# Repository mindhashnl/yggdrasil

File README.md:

# 🌳 Yggdrasil - Hardware Infrastructure

> **⚠️ NOTE:** This repository contains **hardware design files only** (Schematics, PCB Layouts, Gerber files, BOMs, and Mechanical CAD). 
> The software stack is not yet updated to the new hardware.

## 📖 Overview

Yggdrasil is an open-source, modular hardware-in-the-loop (HIL) testing framework designed for continuous integration (CI/CD) of embedded systems. It allows developers to test firmware automatically on real microcontrollers (MCUs) at scale. 

The physical architecture is designed to fit inside a standard **19-inch 3U server rack** and consists of a primary control board, a multiplexing backplane, and hot-swappable target testing blades.

---

## 🧩 System Architecture

The hardware is split into three main modules:

### 1. Mimir (Compute Controller)
The "brain" of the server. It acts as the bridge between the high-level network and the low-level hardware matrix.
* **Core:** Raspberry Pi Compute Module 5 (CM5).
* **Storage:** M.2 NVMe SSD slot for reliable, high-speed storage.
* **Connectivity:** Gigabit Ethernet (RJ45), USB-A, HDMI (for local debugging).
* **Interface:** Connects to the backplane via a custom-pinned PCIe x8 mechanical connector.

### 2. Bifrost (The Backplane)
The routing matrix that connects Mimir to the testing blades. It contains no "smart" compute chips, only routing and switching logic.
* **Switching:** Uses cascaded `74HC595` and `SN74HCS165` shift registers to control `TMUX1511` analog multiplexers.
* **Buses:** Routes shared JTAG, UART, SPI, I2C, CAN, and GPIO lines to any connected blade.
* **Power:** Accepts 12V input and steps it down to 5V and 3.3V rails for the entire system using TPSM33625 modules.
* **Capacity:** Supports up to 16 daughter boards.

### 3. Valkyrie (Daughter Blades)
The Device-Under-Test (DUT) modules. These are inserted into the front of the server.
* **Form Factor:** 110mm x 170mm (excluding PCIe fingers). Fits in custom HDD-style hot-swap trays.
* **Standardization:** Connects to Bifrost using a custom-pinned PCIe x16 mechanical connector.
* **Included Reference Designs:**
  * **Valkyrie-ESP32S3:** A complete testing blade featuring an ESP32-S3, status LEDs, physical buttons, and a hardware identification EEPROM.
  * **Valkyrie-Test:** A diagnostic board with LEDs mapped to every PCIe lane to visually verify multiplexer switching logic.

---

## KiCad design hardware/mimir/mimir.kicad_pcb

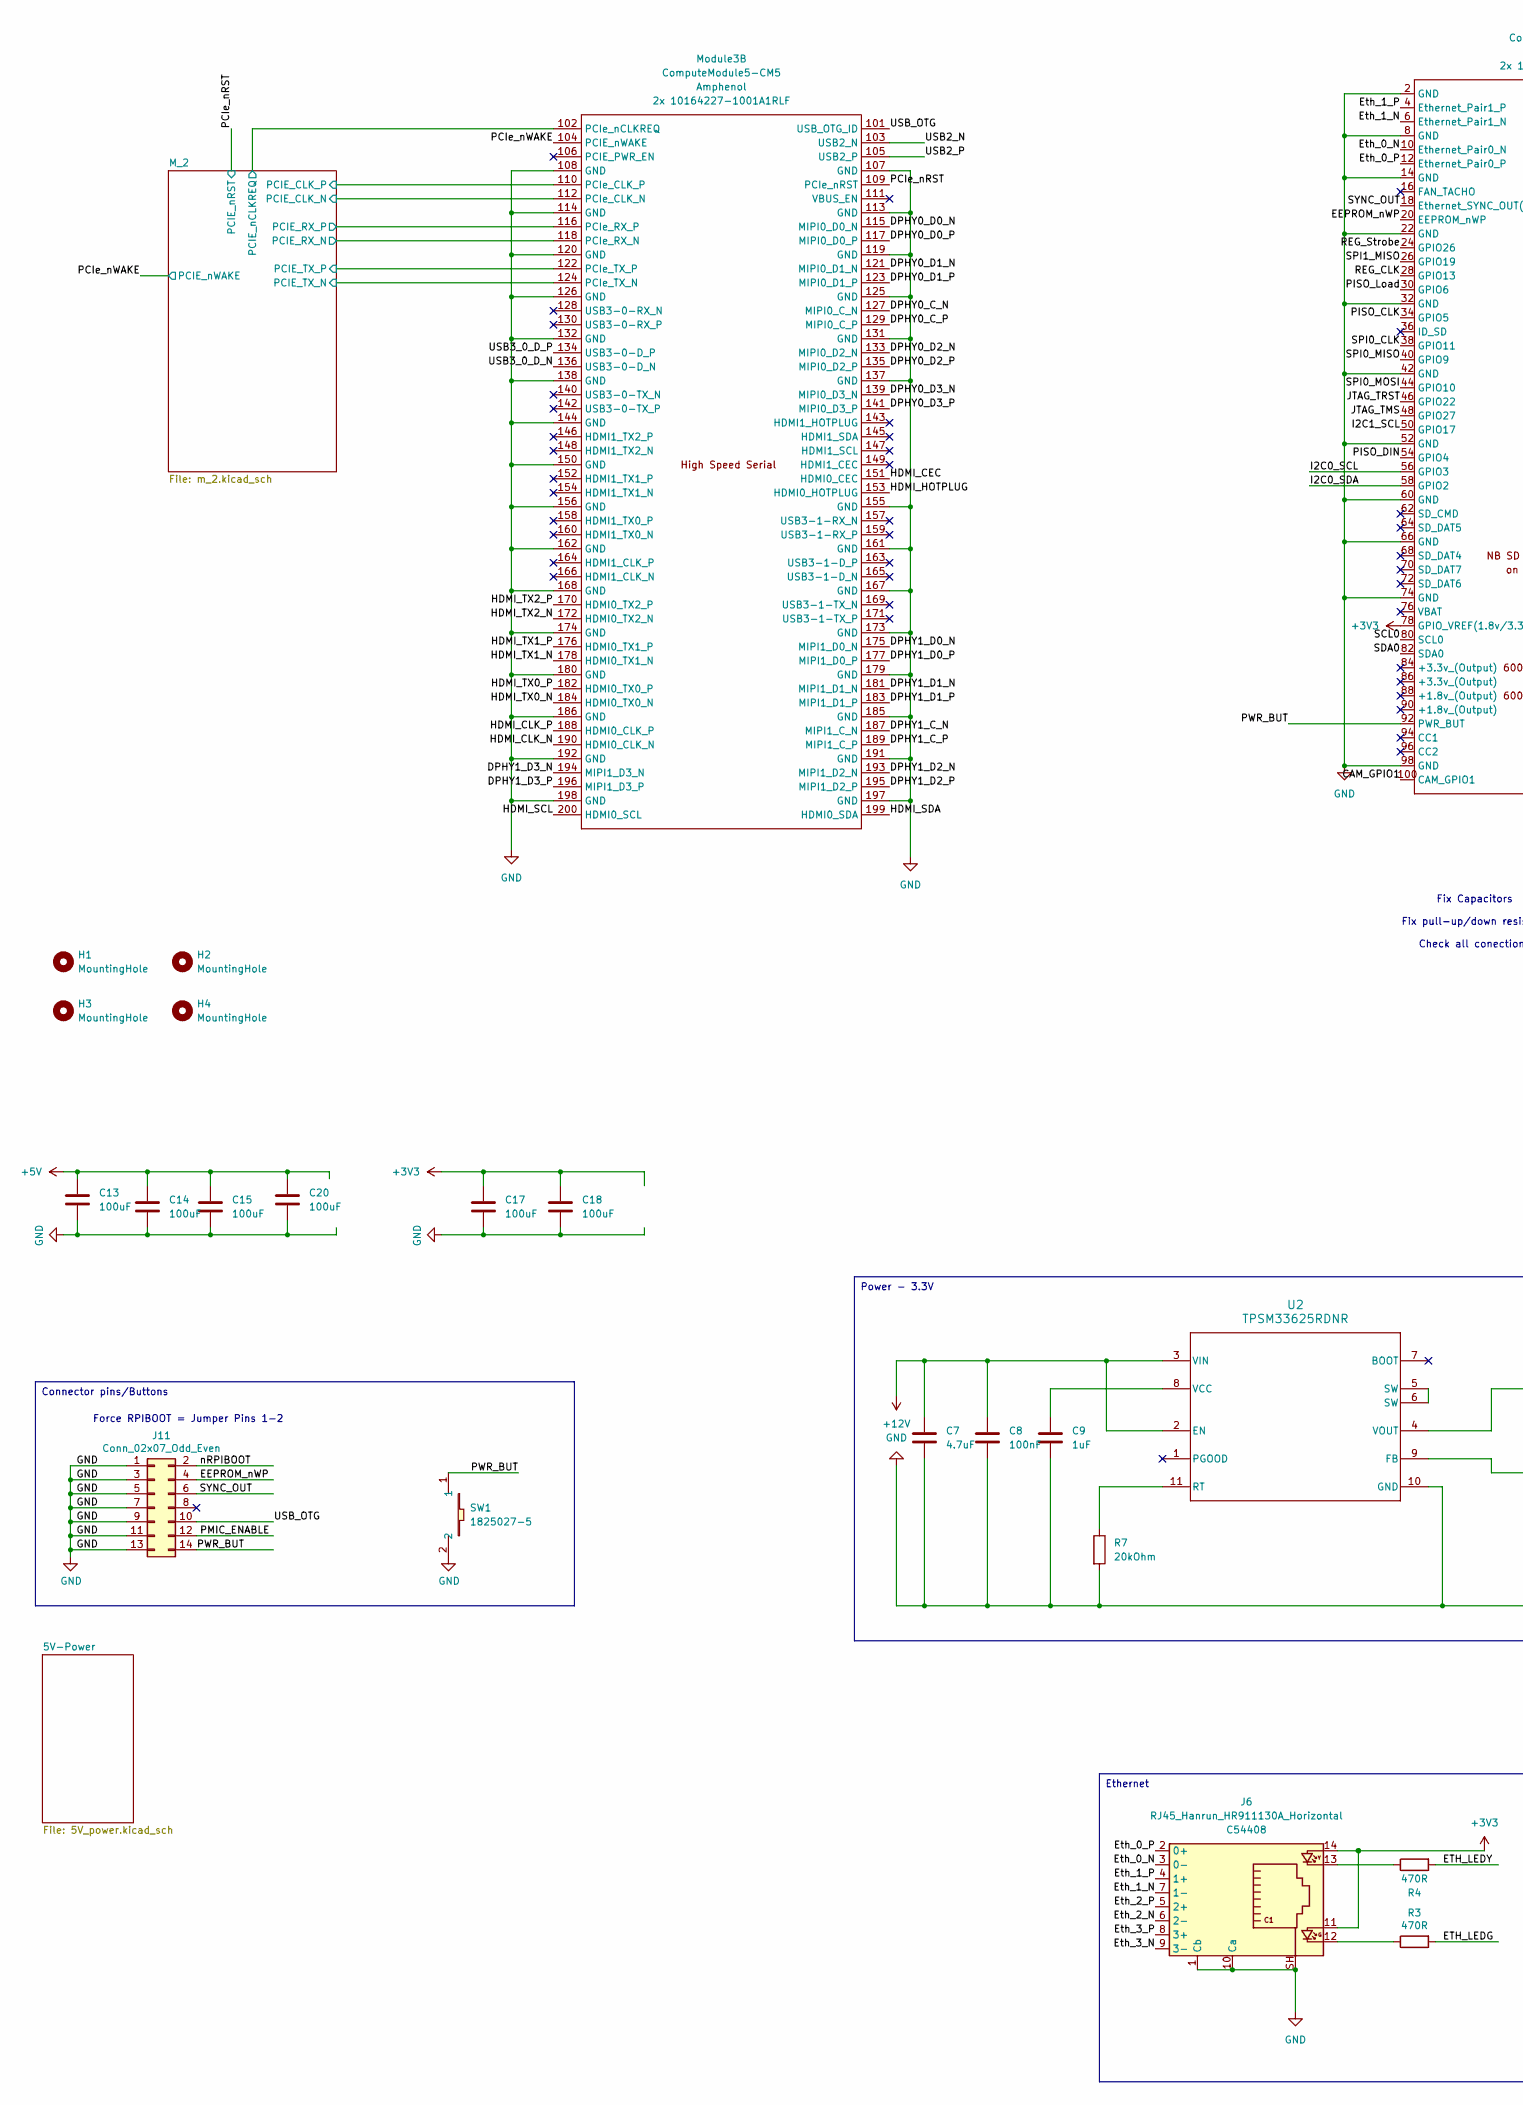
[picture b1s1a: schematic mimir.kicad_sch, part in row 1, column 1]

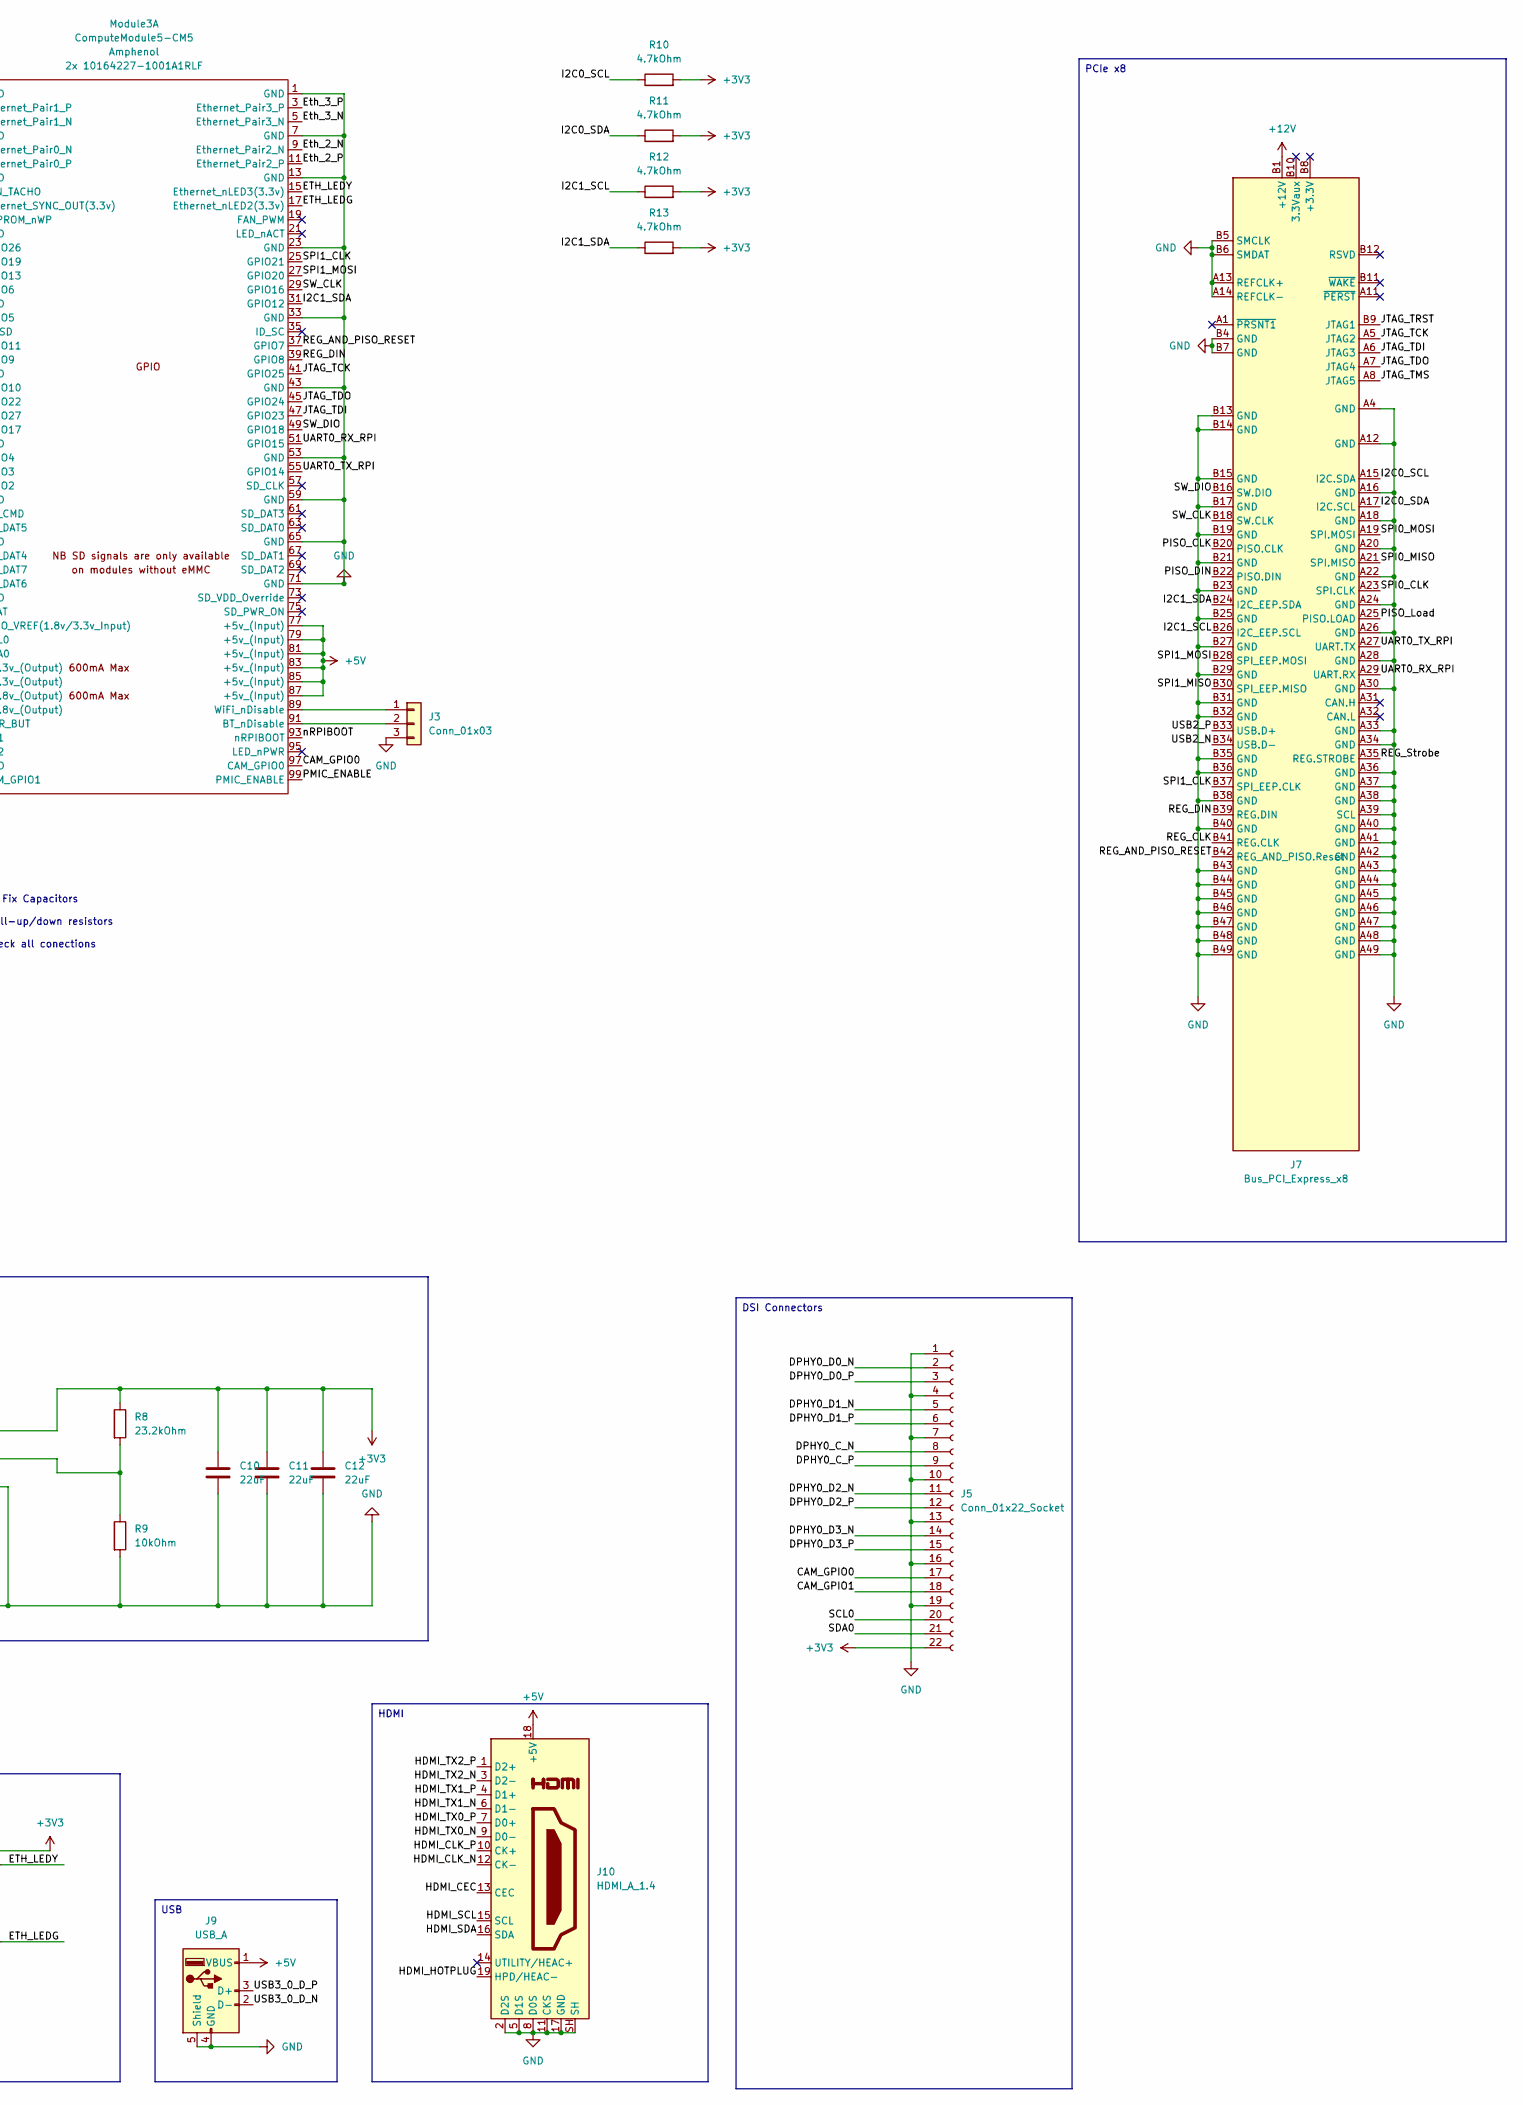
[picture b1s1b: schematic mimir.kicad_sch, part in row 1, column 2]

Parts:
C7: 4.7uF; C_0805_2012Metric
C8: 100nF; C_0805_2012Metric
C9: 1uF; C_0805_2012Metric
C10, C11, C12: 22uF; C_0805_2012Metric
C13, C14, C15, C17, C18, C20: 100uF; C_1210_3225Metric
H1, H2, H3, H4: MountingHole; MountingHole_3.2mm_M3_DIN965_Pad_TopBottom
J3: Conn_01x03; PinHeader_1x03_P2.54mm_Vertical
J5: Conn_01x22_Socket; Hirose_FH12-22S-0.5SH_1x22-1MP_P0.50mm_Horizontal
J6: RJ45_Hanrun_HR911130A_Horizontal; MPN C54408
J7: Bus_PCI_Express_x8; BUS_PCIexpress_x8
J9: USB_A; USB_A_Molex_67643_Horizontal
J10: HDMI_A_1.4; HDMI_A_Molex_208658-1001_Horizontal
J11: Conn_02x07_Odd_Even; PinHeader_2x07_P2.54mm_Vertical; Part Description PinHeader_2x07_P2.54mm_Vertical
Module3: ComputeModule5-CM5; Raspberry-Pi-5-Compute-Module; MPN C597931
R3, R4: 470R; R_0805_2012Metric; Part Description Resistor 470R M1005 1% 63mW
R7: 20kOhm; R_0805_2012Metric
R8: 23.2kOhm; R_0805_2012Metric
R9: 10kOhm; R_0805_2012Metric
R10, R11, R12, R13: 4.7kOhm; R_0805_2012Metric
SW1: 1825027-5; KEY-TH_4P-L7.5-W6.8-P4.50-LS7.2; LCSC Part C86476
U2: TPSM33625RDNR; RDN0011A-MFG_custom

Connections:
+3V3: C10.1, C11.1, C12.1, C17.1, C18.1, J5.22, J6.11, J6.14, Module3.78 (GPIO_VREF(1.8v/3.3v_Input)), R8.1, R10.2, R11.2, R12.2, R13.2, U2.4 (VOUT); also elsewhere on the board
+5V: C13.1, C14.1, C15.1, C20.1, J9.1 (VBUS), J10.18 (+5V), Module3.77 (+5v_(Input)), Module3.79 (+5v_(Input)), Module3.81 (+5v_(Input)), Module3.83 (+5v_(Input)), Module3.85 (+5v_(Input)), Module3.87 (+5v_(Input)); also elsewhere on the board
+12V: C7.1, C8.1, J7.A2 (+12V), J7.A3 (+12V), J7.B1 (+12V), J7.B2 (+12V), J7.B3 (+12V), U2.2 (EN), U2.3 (VIN); also elsewhere on the board
/CAM_GPIO0: J5.17, Module3.97 (CAM_GPIO0)
/CAM_GPIO1: J5.18, Module3.100 (CAM_GPIO1)
/DPHY0_C_N: J5.8, Module3.127 (MIPI0_C_N)
/DPHY0_C_P: J5.9, Module3.129 (MIPI0_C_P)
/DPHY0_D0_N: J5.2, Module3.115 (MIPI0_D0_N)
/DPHY0_D0_P: J5.3, Module3.117 (MIPI0_D0_P)
/DPHY0_D1_N: J5.5, Module3.121 (MIPI0_D1_N)
/DPHY0_D1_P: J5.6, Module3.123 (MIPI0_D1_P)
/DPHY0_D2_N: J5.11, Module3.133 (MIPI0_D2_N)
/DPHY0_D2_P: J5.12, Module3.135 (MIPI0_D2_P)
/DPHY0_D3_N: J5.14, Module3.139 (MIPI0_D3_N)
/DPHY0_D3_P: J5.15, Module3.141 (MIPI0_D3_P)
/DPHY1_C_N: Module3.187 (MIPI1_C_N)
/DPHY1_C_P: Module3.189 (MIPI1_C_P)
/DPHY1_D0_N: Module3.175 (MIPI1_D0_N)
/DPHY1_D0_P: Module3.177 (MIPI1_D0_P)
/DPHY1_D1_N: Module3.181 (MIPI1_D1_N)
/DPHY1_D1_P: Module3.183 (MIPI1_D1_P)
/DPHY1_D2_N: Module3.193 (MIPI1_D2_N)
/DPHY1_D2_P: Module3.195 (MIPI1_D2_P)
/DPHY1_D3_N: Module3.194 (MIPI1_D3_N)
/DPHY1_D3_P: Module3.196 (MIPI1_D3_P)
/EEPROM_nWP: J11.4, Module3.20 (EEPROM_nWP)
/ETH_LEDG: Module3.17 (Ethernet_nLED2(3.3v)), R3.2
/ETH_LEDY: Module3.15 (Ethernet_nLED3(3.3v)), R4.2
/Eth_0_N: J6.3 (0-), Module3.10 (Ethernet_Pair0_N)
/Eth_0_P: J6.2 (0+), Module3.12 (Ethernet_Pair0_P)
/Eth_1_N: J6.7 (1-), Module3.6 (Ethernet_Pair1_N)
/Eth_1_P: J6.4 (1+), Module3.4 (Ethernet_Pair1_P)
/Eth_2_N: J6.6 (2-), Module3.9 (Ethernet_Pair2_N)
/Eth_2_P: J6.5 (2+), Module3.11 (Ethernet_Pair2_P)
/Eth_3_N: J6.9 (3-), Module3.5 (Ethernet_Pair3_N)
/Eth_3_P: J6.8 (3+), Module3.3 (Ethernet_Pair3_P)
/HDMI_CEC: J10.13 (CEC), Module3.151 (HDMI0_CEC)
/HDMI_CLK_N: J10.12 (CK-), Module3.190 (HDMI0_CLK_N)
/HDMI_CLK_P: J10.10 (CK+), Module3.188 (HDMI0_CLK_P)
/HDMI_HOTPLUG: J10.19 (HPD/HEAC-), Module3.153 (HDMI0_HOTPLUG)
/HDMI_SCL: J10.15 (SCL), Module3.200 (HDMI0_SCL)
/HDMI_SDA: J10.16 (SDA), Module3.199 (HDMI0_SDA)
/HDMI_TX0_N: J10.9 (D0-), Module3.184 (HDMI0_TX0_N)
/HDMI_TX0_P: J10.7 (D0+), Module3.182 (HDMI0_TX0_P)
/HDMI_TX1_N: J10.6 (D1-), Module3.178 (HDMI0_TX1_N)
/HDMI_TX1_P: J10.4 (D1+), Module3.176 (HDMI0_TX1_P)
/HDMI_TX2_N: J10.3 (D2-), Module3.172 (HDMI0_TX2_N)
/HDMI_TX2_P: J10.1 (D2+), Module3.170 (HDMI0_TX2_P)
/I2C0_SCL: J7.A15 (I2C.SDA), Module3.56 (GPIO3), R10.1
/I2C0_SDA: J7.A17 (I2C.SCL), Module3.58 (GPIO2), R11.1
/I2C1_SCL: J7.B26 (I2C_EEP.SCL), Module3.50 (GPIO17), R12.1
/I2C1_SDA: J7.B24 (I2C_EEP.SDA), Module3.31 (GPIO12), R13.1
/JTAG_TCK: J7.A5 (JTAG2), Module3.41 (GPIO25)
/JTAG_TDI: J7.A6 (JTAG3), Module3.47 (GPIO23)
/JTAG_TDO: J7.A7 (JTAG4), Module3.45 (GPIO24)
/JTAG_TMS: J7.A8 (JTAG5), Module3.48 (GPIO27)
/JTAG_TRST: J7.B9 (JTAG1), Module3.46 (GPIO22)
/M_2/PCIE_CLK_N: Module3.112 (PCIe_CLK_N); also elsewhere on the board
/M_2/PCIE_CLK_P: Module3.110 (PCIe_CLK_P); also elsewhere on the board
/M_2/PCIE_RX_N: Module3.118 (PCIe_RX_N); also elsewhere on the board
/M_2/PCIE_RX_P: Module3.116 (PCIe_RX_P); also elsewhere on the board
/M_2/PCIE_TX_N: Module3.124 (PCIe_TX_N); also elsewhere on the board
/M_2/PCIE_TX_P: Module3.122 (PCIe_TX_P); also elsewhere on the board
/M_2/PCIE_nCLKREQ: Module3.102 (PCIe_nCLKREQ); also elsewhere on the board
/PCIe_nRST: Module3.109 (PCIe_nRST); also elsewhere on the board
/PCIe_nWAKE: Module3.104 (PCIE_nWAKE); also elsewhere on the board
/PISO_CLK: J7.B20 (PISO.CLK), Module3.34 (GPIO5)
/PISO_DIN: J7.B22 (PISO.DIN), Module3.54 (GPIO4)
/PISO_Load: J7.A25 (PISO.LOAD), Module3.30 (GPIO6)
/PMIC_ENABLE: J11.12, Module3.99 (PMIC_ENABLE)
/PWR_BUT: J11.14, Module3.92 (PWR_BUT), SW1.1
/REG_AND_PISO_RESET: J7.B42 (REG_AND_PISO.Reset), Module3.37 (GPIO7)
/REG_CLK: J7.B41 (REG.CLK), Module3.28 (GPIO13)
/REG_DIN: J7.B39 (REG.DIN), Module3.39 (GPIO8)
/REG_Strobe: J7.A35 (REG.STROBE), Module3.24 (GPIO26)
/SCL0: J5.20, Module3.80 (SCL0)
/SDA0: J5.21, Module3.82 (SDA0)
/SPI0_CLK: J7.A23 (SPI.CLK), Module3.38 (GPIO11)
/SPI0_MISO: J7.A21 (SPI.MISO), Module3.40 (GPIO9)
/SPI0_MOSI: J7.A19 (SPI.MOSI), Module3.44 (GPIO10)
/SPI1_CLK: J7.B37 (SPI_EEP.CLK), Module3.25 (GPIO21)
/SPI1_MISO: J7.B30 (SPI_EEP.MISO), Module3.26 (GPIO19)
/SPI1_MOSI: J7.B28 (SPI_EEP.MOSI), Module3.27 (GPIO20)
/SW_CLK: J7.B18 (SW.CLK), Module3.29 (GPIO16)
/SW_DIO: J7.B16 (SW.DIO), Module3.49 (GPIO18)
/SYNC_OUT: J11.6, Module3.18 (Ethernet_SYNC_OUT(3.3v))
/UART0_RX_RPI: J7.A29 (UART.RX), Module3.51 (GPIO15)
/UART0_TX_RPI: J7.A27 (UART.TX), Module3.55 (GPIO14)
/USB2_N: J7.B34 (USB.D-), Module3.103 (USB2_N)
/USB2_P: J7.B33 (USB.D+), Module3.105 (USB2_P)
/USB3_0_D_N: J9.2 (D-), Module3.136 (USB3-0-D_N)
/USB3_0_D_P: J9.3 (D+), Module3.134 (USB3-0-D_P)
/USB_OTG: J11.10, Module3.101 (USB_OTG_ID)
/nRPIBOOT: J11.2, Module3.93 (nRPIBOOT)
GND: C7.2, C8.2, C9.2, C10.2, C11.2, C12.2, C13.2, C14.2, C15.2, C17.2, C18.2, C20.2, J3.3, J5.1, J5.4, J5.7, J5.10, J5.13, J5.16, J5.19, J6.1 (Cb), J6.10 (Ca), J6.SH, J7.A4 (GND), J7.A12 (GND), J7.A13 (REFCLK+), J7.A14 (REFCLK-), J7.A16 (GND), J7.A18 (GND), J7.A20 (GND), J7.A22 (GND), J7.A24 (GND), J7.A26 (GND), J7.A28 (GND), J7.A30 (GND), J7.A33 (GND), J7.A34 (GND), J7.A36 (GND), J7.A37 (GND), J7.A38 (GND), J7.A39 (SCL), J7.A40 (GND), J7.A41 (GND), J7.A42 (GND), J7.A43 (GND), J7.A44 (GND), J7.A45 (GND), J7.A46 (GND), J7.A47 (GND), J7.A48 (GND), J7.A49 (GND), J7.B4 (GND), J7.B5 (SMCLK), J7.B6 (SMDAT), J7.B7 (GND), J7.B13 (GND), J7.B14 (GND), J7.B15 (GND), J7.B17 (GND), J7.B19 (GND), J7.B21 (GND), J7.B23 (GND), J7.B25 (GND), J7.B27 (GND), J7.B29 (GND), J7.B31 (GND), J7.B32 (GND), J7.B35 (GND), J7.B36 (GND), J7.B38 (GND), J7.B40 (GND), J7.B43 (GND), J7.B44 (GND), J7.B45 (GND), J7.B46 (GND), J7.B47 (GND), J7.B48 (GND), J7.B49 (GND), J9.4 (GND), J9.5 (Shield), J10.2 (D2S), J10.5 (D1S), J10.8 (D0S), J10.11 (CKS), J10.17 (GND), J10.SH, J11.1, J11.3, J11.5, J11.7, J11.9, J11.11, J11.13, Module3.1 (GND), Module3.2 (GND), Module3.7 (GND), Module3.8 (GND), Module3.13 (GND), Module3.14 (GND), Module3.22 (GND), Module3.23 (GND), Module3.32 (GND), Module3.33 (GND), Module3.42 (GND), Module3.43 (GND), Module3.52 (GND), Module3.53 (GND), Module3.59 (GND), Module3.60 (GND), Module3.65 (GND), Module3.66 (GND), Module3.71 (GND), Module3.74 (GND), Module3.98 (GND), Module3.107 (GND), Module3.108 (GND), Module3.113 (GND), Module3.114 (GND), Module3.119 (GND), Module3.120 (GND), Module3.125 (GND), Module3.126 (GND), Module3.131 (GND), Module3.132 (GND), Module3.137 (GND), Module3.138 (GND), Module3.144 (GND), Module3.150 (GND), Module3.155 (GND), Module3.156 (GND), Module3.161 (GND), Module3.162 (GND), Module3.167 (GND), Module3.168 (GND), Module3.173 (GND), Module3.174 (GND), Module3.179 (GND), Module3.180 (GND), Module3.185 (GND), Module3.186 (GND), Module3.191 (GND), Module3.192 (GND), Module3.197 (GND), Module3.198 (GND), R7.2, R9.2, SW1.2, U2.10 (GND); also elsewhere on the board
unnamed: J3.1, Module3.89 (WiFi_nDisable)
unnamed: J3.2, Module3.91 (BT_nDisable)
unnamed: J6.12, R3.1
unnamed: J6.13, R4.1
unnamed: R8.2, R9.1, U2.9 (FB)
unnamed: R7.1, U2.11 (RT)
unnamed: U2.5 (SW), U2.6 (SW)
unnamed: C9.1, U2.8 (VCC)

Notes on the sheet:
Ethernet
Connector pins/Buttons
USB
Power - 3.3V
HDMI
PCIe x8
DSI Connectors
Force RPIBOOT = Jumper Pins 1-2
Fix Capacitors Fix pull-up/down resistors Check all conections

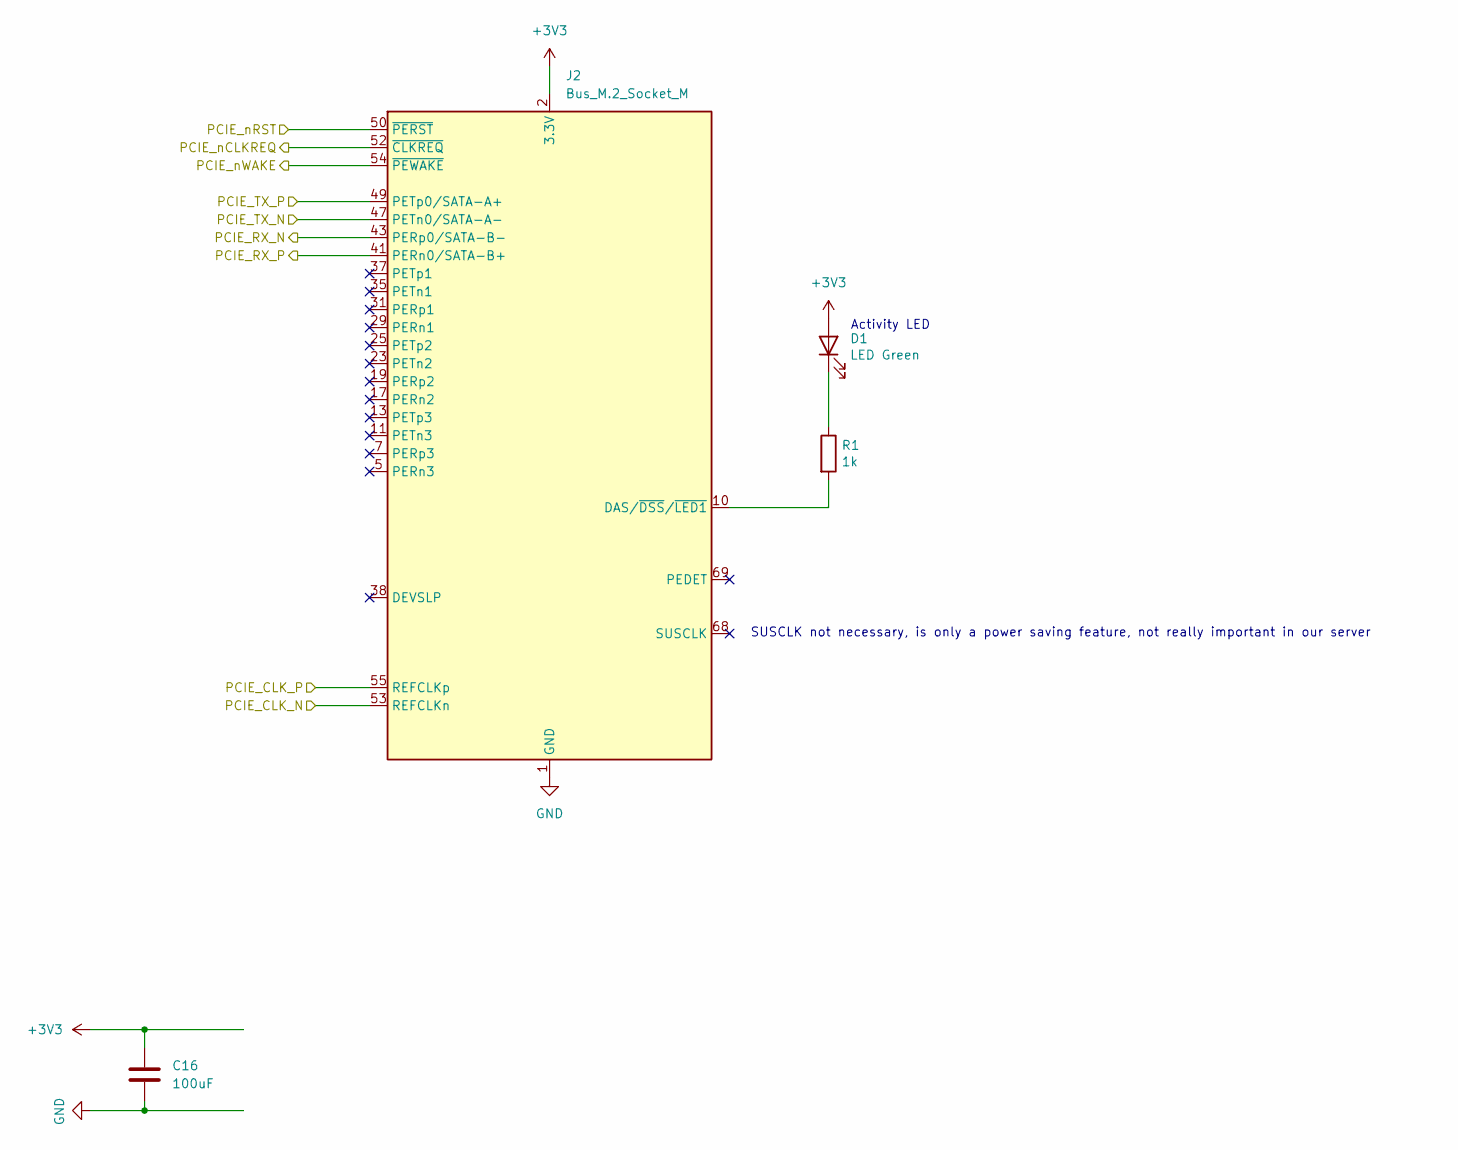
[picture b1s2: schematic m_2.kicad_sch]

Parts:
C16: 100uF; C_1210_3225Metric
D1: LED Green; LED_0603_1608Metric; Part Description Green 572nm LED Indication - Discrete 2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
J2: Bus_M.2_Socket_M; M.2 M Key socket
R1: 1k; R_0805_2012Metric; Part Description Resistor 1K M1005 1% 63mW

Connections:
+3V3: C16.1, D1.2 (A), J2.2 (3.3V), J2.4 (3.3V), J2.12 (3.3V), J2.14 (3.3V), J2.16 (3.3V), J2.18 (3.3V), J2.70 (3.3V), J2.72 (3.3V), J2.74 (3.3V); also elsewhere on the board
/M_2/PCIE_CLK_N: J2.53 (REFCLKn); also elsewhere on the board
/M_2/PCIE_CLK_P: J2.55 (REFCLKp); also elsewhere on the board
/M_2/PCIE_RX_N: J2.43 (PERp0/SATA-B-); also elsewhere on the board
/M_2/PCIE_RX_P: J2.41 (PERn0/SATA-B+); also elsewhere on the board
/M_2/PCIE_TX_N: J2.47 (PETn0/SATA-A-); also elsewhere on the board
/M_2/PCIE_TX_P: J2.49 (PETp0/SATA-A+); also elsewhere on the board
/M_2/PCIE_nCLKREQ: J2.52 (~CLKREQ); also elsewhere on the board
/PCIe_nRST: J2.50 (~PERST); also elsewhere on the board
/PCIe_nWAKE: J2.54 (~PEWAKE); also elsewhere on the board
GND: C16.2, J2.1 (GND), J2.3 (GND), J2.9 (GND), J2.15 (GND), J2.21 (GND), J2.27 (GND), J2.33 (GND), J2.39 (GND), J2.45 (GND), J2.51 (GND), J2.57 (GND), J2.71 (GND), J2.73 (GND), J2.75 (GND); also elsewhere on the board
unnamed: D1.1 (K), R1.1
unnamed: J2.10 (DAS/~DSS/~LED1), R1.2

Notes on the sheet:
SUSCLK not necessary, is only a power saving feature, not really important in our server
Activity LED

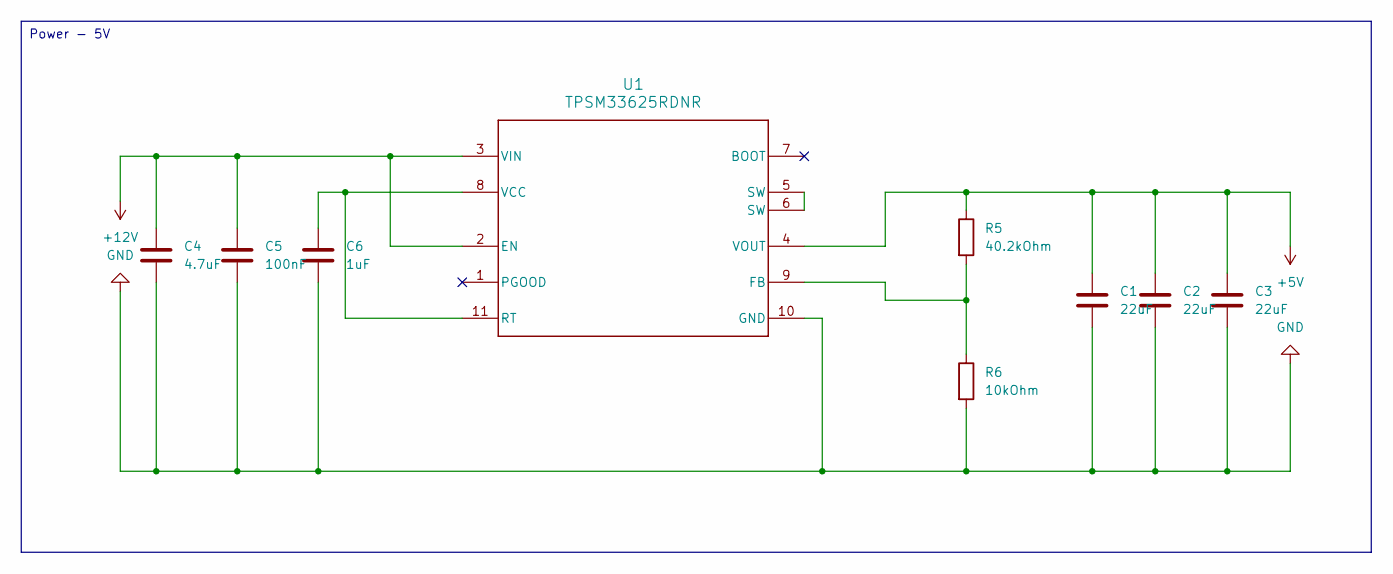
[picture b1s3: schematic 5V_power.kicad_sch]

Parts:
C1, C2, C3: 22uF; C_0805_2012Metric
C4: 4.7uF; C_0805_2012Metric
C5: 100nF; C_0805_2012Metric
C6: 1uF; C_0805_2012Metric
R5: 40.2kOhm; R_0805_2012Metric
R6: 10kOhm; R_0805_2012Metric
U1: TPSM33625RDNR; RDN0011A-MFG_custom

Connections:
+5V: C1.1, C2.1, C3.1, R5.1, U1.4 (VOUT); also elsewhere on the board
+12V: C4.1, C5.1, U1.2 (EN), U1.3 (VIN); also elsewhere on the board
GND: C1.2, C2.2, C3.2, C4.2, C5.2, C6.2, R6.2, U1.10 (GND); also elsewhere on the board
unnamed: R5.2, R6.1, U1.9 (FB)
unnamed: C6.1, U1.8 (VCC), U1.11 (RT)
unnamed: U1.5 (SW), U1.6 (SW)

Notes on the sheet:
Power - 5V

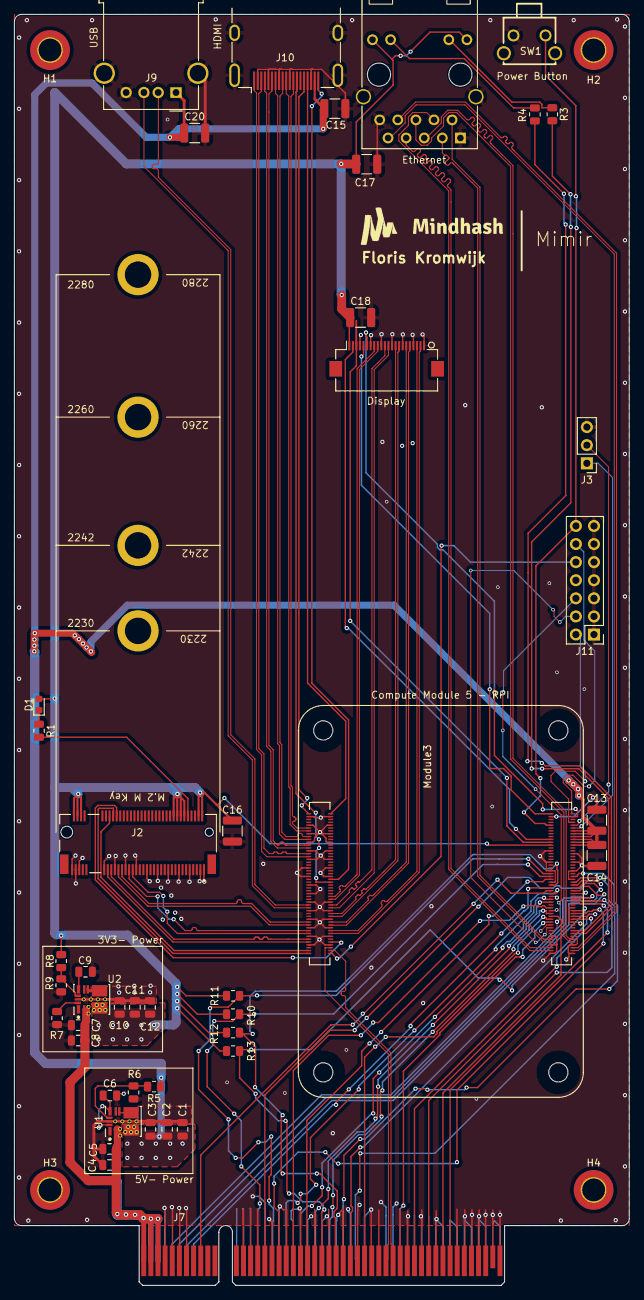
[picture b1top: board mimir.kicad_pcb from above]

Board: 4 copper layers, 86.3 x 178.4 mm, 48 parts (0 on the bottom side), 98 nets.

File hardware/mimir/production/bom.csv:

Designator,Footprint,Quantity,Value,LCSC Part #
"C1, C10, C11, C12, C2, C3",805,6,22uF,
"C13, C14, C15, C16, C17, C18, C20",1210,7,100uF,
"C4, C7",805,2,4.7uF,
"C5, C8",805,2,100nF,
"C6, C9",805,2,1uF,
D1,603,1,LED Green,
J10,HDMI_A_Molex_208658-1001_Horizontal,1,HDMI_A_1.4,
J11,PinHeader_2x07_P2.54mm_Vertical,1,Conn_02x07_Odd_Even,
J2,M.2 M Key socket,1,Bus_M.2_Socket_M,
J3,PinHeader_1x03_P2.54mm_Vertical,1,Conn_01x03,
J5,Hirose_FH12-22S-0.5SH_1x22-1MP_P0.50mm_Horizontal,2,Conn_01x22_Socket,
J6,RJ45_Hanrun_HR911130A_Horizontal,1,RJ45_Hanrun_HR911130A_Horizontal,C54408
J7,BUS_PCIexpress_x8,1,Bus_PCI_Express_x8,
J9,USB_A_Molex_67643_Horizontal,1,USB_A,
"MODULE3, MODULE4",Raspberry-Pi-5-Compute-Module,2,ComputeModule5-CM5,C597931
R1,805,1,1k,
"R10, R11, R12, R13",805,4,4.7kOhm,
"R3, R4",805,2,470R,
R5,805,1,40.2kOhm,
"R6, R9",805,2,10kOhm,
R7,805,1,20kOhm,
R8,805,1,23.2kOhm,
SW1,KEY-TH_4P-L7.5-W6.8-P4.50-LS7.2,1,1825027-5,
"U1, U2",RDN0011A-MFG_custom,2,TPSM33625RDNR,
